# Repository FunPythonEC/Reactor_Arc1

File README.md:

# Reactor_Arc1
Proyecto para simular el Reactor Arc mediante un conjunto de leds WS2812B controlados con un ESP01. 
El diseño esta realizado con kicad.

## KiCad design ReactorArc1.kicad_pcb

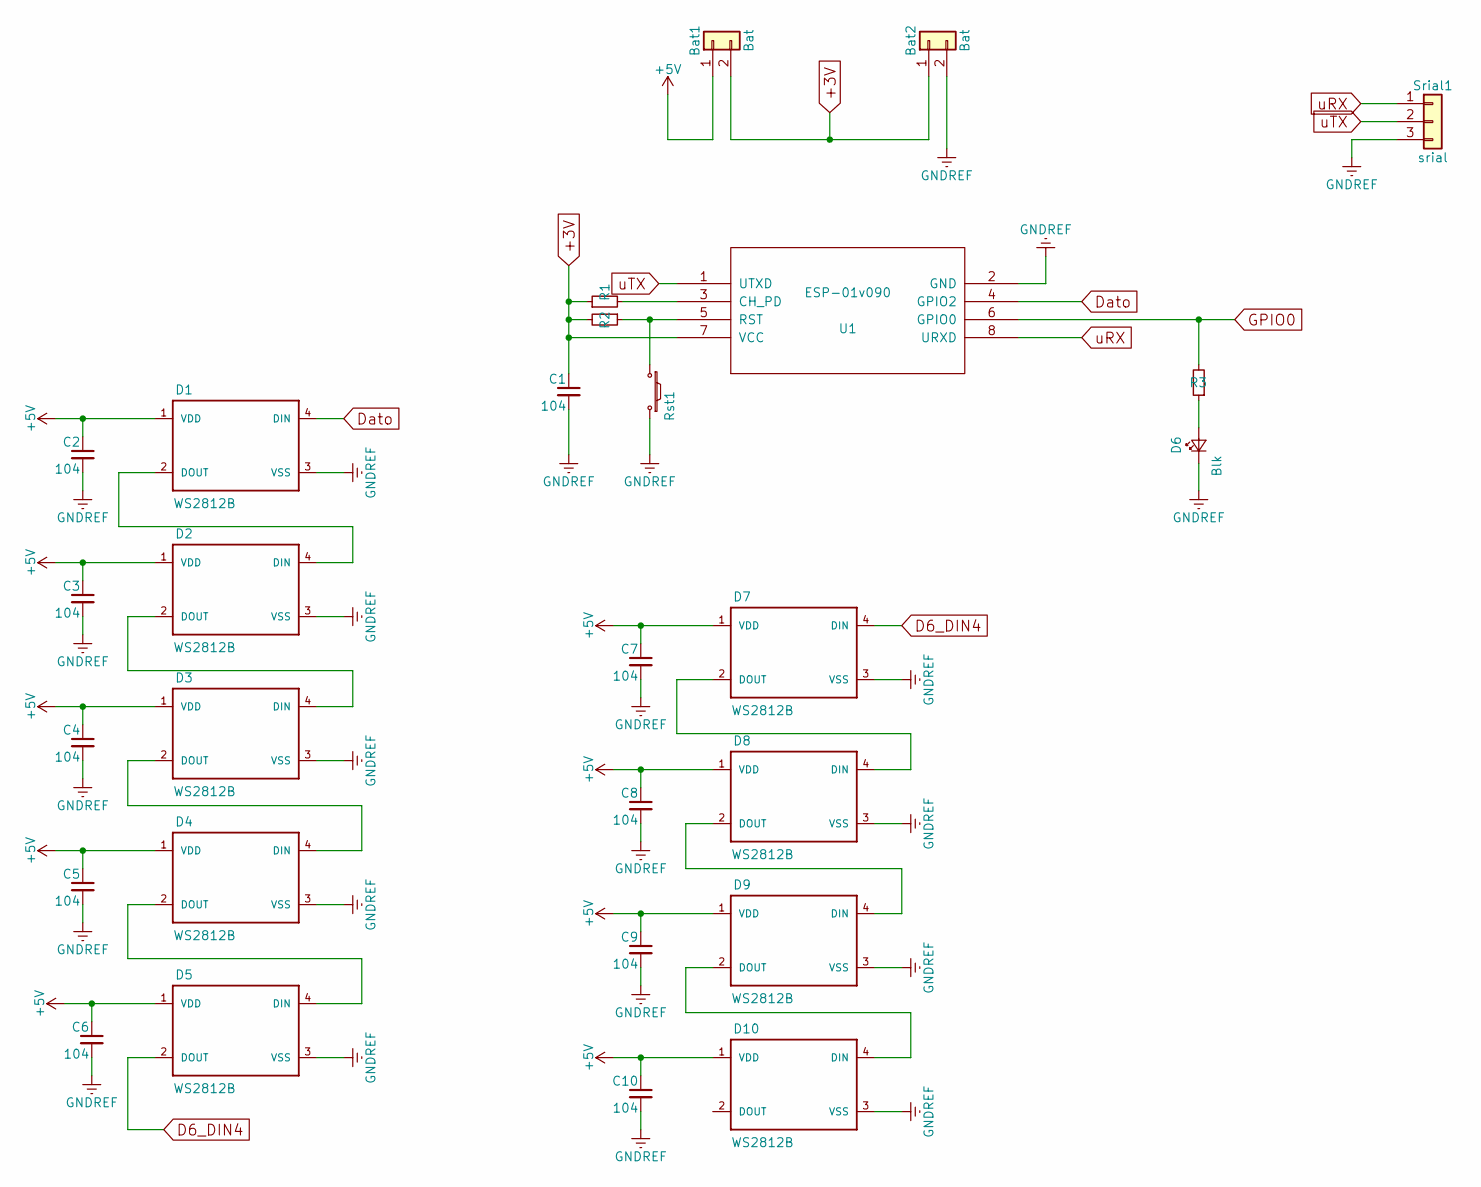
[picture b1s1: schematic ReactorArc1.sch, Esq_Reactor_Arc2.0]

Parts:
Bat1, Bat2: Bat; Molex_KK-6410-02_02x2.54mm_Straight
C1, C2, C3, C4, C5, C6, C7, C8, C9, C10: 104; C_0805_HandSoldering
D1, D2, D3, D4, D5, D7, D8, D9, D10: WS2812B
D6: Blk; LED_0805_HandSoldering
R1, R2: 10k; R_0805_HandSoldering
R3: 220; R_0805_HandSoldering
Rst1: SW_PUSH_SMALL_H; SW_SPST_B3U-1000P
Srial1: srial; Molex_KK-6410-03_03x2.54mm_Straight
U1: ESP-01v090; ESP-01

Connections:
+3V: Bat1.2, Bat2.1, C1.1, R1.1, R2.2, U1.7 (VCC)
+5V: Bat1.1, C2.1, C3.1, C4.1, C5.1, C6.1, C7.1, C8.1, C9.1, C10.1, D1.1 (VDD), D2.1 (VDD), D3.1 (VDD), D4.1 (VDD), D5.1 (VDD), D7.1 (VDD), D8.1 (VDD), D9.1 (VDD), D10.1 (VDD)
D6_DIN4: D5.2 (DOUT), D7.4 (DIN)
Dato: D1.4 (DIN), U1.4 (GPIO2)
GNDREF: Bat2.2, C1.2, C2.2, C3.2, C4.2, C5.2, C6.2, C7.2, C8.2, C9.2, C10.2, D1.3 (VSS), D2.3 (VSS), D3.3 (VSS), D4.3 (VSS), D5.3 (VSS), D6.1 (K), D7.3 (VSS), D8.3 (VSS), D9.3 (VSS), D10.3 (VSS), Rst1.2, Srial1.3, U1.2 (GND); also elsewhere on the board
GPIO0: R3.2, U1.6 (GPIO0)
unnamed: D1.2 (DOUT), D2.4 (DIN)
unnamed: D2.2 (DOUT), D3.4 (DIN)
unnamed: D3.2 (DOUT), D4.4 (DIN)
unnamed: D4.2 (DOUT), D5.4 (DIN)
unnamed: D6.2 (A), R3.1
unnamed: D7.2 (DOUT), D8.4 (DIN)
unnamed: D8.2 (DOUT), D9.4 (DIN)
unnamed: D9.2 (DOUT), D10.4 (DIN)
unnamed: R1.2, U1.3 (CH_PD)
unnamed: R2.1, Rst1.1, U1.5 (RST)
uRX: Srial1.1, U1.8 (URXD); also elsewhere on the board
uTX: Srial1.2, U1.1 (UTXD); also elsewhere on the board

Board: 2 copper layers, 28 parts (0 on the bottom side), 18 nets, no tracks yet.

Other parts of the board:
Srial: srial; Molex_KK-6410-03_03x2.54mm_Straight

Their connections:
GNDREF: Srial.3; also elsewhere on the board
uRX: Srial.1; also elsewhere on the board
uTX: Srial.2; also elsewhere on the board
